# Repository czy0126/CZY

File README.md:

# CZY — 48 V → 约 2 V 薄型固定变比 DCX

**D1 当前设计目标：** 约 24:1 固定比、100 A 输出目标、整机高度 ≤16 mm；成本暂不限制。D2 的 120 A 与 D3 的 ≤10 mm 均后置，保护、绝缘、载流与制造签核不可省。

> **当前研发分支：[`feat/d1-fab-package`](https://github.com/czy0126/CZY/tree/feat/d1-fab-package)。默认 `main` 仍是历史快照。当前 D1 为 `NOT_FOR_FAB`；真实样机尚未获得投板或额定许可。**

## 从这里开始（不用翻旧审核报告）

1. **[D1 当前交接面板](docs/D1_CURRENT.md)**：唯一当前可编辑 G1 原生 PCB、已发生的 ECO、三条并行任务及下一次操作/验收。
2. **[D1 已决事项与重开条件](docs/D1_DECISIONS.md)**：R8/R6、Lr XY、九根布线预检、100 A 铜路等已经确认的边界；禁止重复审查同一证据。
3. **[第49章：D1 G1→G2→G3 交付合同](docs/D1_EXECUTION_KIT/49_D1主功率板PCB唯一执行计划_2026-11-09.md)**：阶段目标、冻结条件与实际制造要求；其 11/9 日期快照不覆盖当前 G1 读回。
4. **[历史技术资料索引](docs/D1_REFERENCE_INDEX.md)**：资料在哪里、哪些只作参考。原 README 的长篇历史更新已[归档](docs/archive/README_D1_branch_before_single_entry_2026-11-10.md)，保留所有技术原文和链接。

**唯一任务入口：** [Issue #4 总交付](https://github.com/czy0126/CZY/issues/4)，以及 [#9 原生 PCB/器件](https://github.com/czy0126/CZY/issues/9)、[#12 磁件与接口](https://github.com/czy0126/CZY/issues/12)、[#36 D0 保护](https://github.com/czy0126/CZY/issues/36)。**同时最多 A/B/C 三个工程工作包**；不为“再次审核/继续优化”新建总计划。

## 实际应该先做什么

**A 线优先：** 9条控制小信号增量已完成原生重开验收，未连接206→199，Physical 0、Netlist仍1；见[同CAD审核回执](hardware/dcx_main/g1/lr_signal_review_report.json)。下一步处理原生Import Changes逐位号差异、实体Cout和100 A两极铜路，不重复重画已有短线。

```powershell
python -m pytest tools/test_g1_copper_coverage.py tools/test_g1_driver_route_plan.py -q
```

上述测试是回归检查，不替代原生DRC；本轮信号候选及失败回执全部保留，尚待随本轮提交提升基线。B（真实 Maxwell/实体 PAD）与 C（D0 真实关断）并行，不得以模拟或脚本绿色替代实际硬件证据。

**工程和开发规则：** [`CLAUDE.md`](CLAUDE.md) · [`docs/agent/EDA.md`](docs/agent/EDA.md) · [PR 模板](.github/PULL_REQUEST_TEMPLATE.md)。任何 PR 应说明真实产物的**改动前后、原始证据和下一次实际交付**。仅更换“最新计划”标题或重复风险总结不算里程碑。

**制造许可唯一来源：** [`hardware/dcx_main/d1_fabrication_gate.json`](hardware/dcx_main/d1_fabrication_gate.json) 及其相同 CAD 修订版的独立审核证据；历史 JSON 不能混用为 G1 的签核。

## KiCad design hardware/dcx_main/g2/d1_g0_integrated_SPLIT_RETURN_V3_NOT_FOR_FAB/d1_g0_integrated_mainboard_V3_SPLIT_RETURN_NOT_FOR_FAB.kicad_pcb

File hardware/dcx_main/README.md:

# DCX 主功率板 —— 原生原理图（A1）

> **最新状态：NOT_FOR_FAB / A1-WIP。** 本目录已移入当前开发分支，保留嘉立创原生 `.eprj2` 和真实焊盘比对。**`netlist_compare.json:readiness=PARTIAL_PASS` 不是完整原理图或投板验收。**
> 17 个 BOM 真实外围（R7–R10、C13、C101–C112）与**五只磁件（T1–T4、CT）**都已画进原生原理图并逐焊盘核对；
> 但外围仍是**值/MPN 占位件**，磁件的引脚号是**逻辑端子名**而不是厂商端子图，物理端子号/极性、
> GUI ERC 与带网 PCB 全部未完成。详见 [磁件符号逻辑合同](magnetics_symbol_contract.json)、[61 件真实选型登记表](component_decision_register.json)、[厂家 24 个端子回填表](vendor_terminal_request.json) 和 [外部阻塞解除与执行协议](../../docs/D1_外部阻塞解除与测试交付_2026-11-02.md)。

这是 `design/v3/pcb/board_netlist.csv`（由 v3 deck 派生的**金网表**）在嘉立创 EDA Pro 里的
原生可编辑原理图，不是一份新的设计。器件、网络、位号全部来自金网表；本目录只解决一件事：
把 SPICE 的 `G/S/D` 引脚名落到真实封装的**具体焊盘**上，并证明落对了。

项目文件：`dcx_main_board.eprj2`（嘉立创 EDA Pro 4.1.60，`.eprj2` 是 SQLite）。
打开方式：复制到嘉立创客户端的工程目录（本项目已改为 `D:\workshop\LCEDA-Pro\projects\`，
见 `%USERPROFILE%\Documents\LCEDA-Pro\config.json` 的 `APP_PROJECT_DIR`），在客户端里打开即可编辑。
**本仓库只有原理图，没有 PCB**——headless 下 PCB 相关 API 不可用，见下。

## 已验证的结论

| 结论 | 证据 |
|------|------|
| **83 个位号**已放置：金网表 66 只 + BOM 真实外围 17 只，**285 个焊盘**全部有归属（280 个接线、5 个按设计留空） | `pin_footprint_review.csv` |
| 按 A1 任务卡的**六个功能块**绘制，每块有标题文字，块内按功能排列 | `gen/slice_00.js` 的 `labels` |
| 金网表的 193 个引脚展开成 **245 个焊盘**，逐焊盘比对**无一错接、无一漏接** | `netlist_compare.json:pads_checked` |
| 17 个外围的 **34 个焊盘**按 `pin_connections.csv` 连接并单独计数，不混进金网表的 245 | `peripheral_pads_checked` |
| U2（UCC27282）裸露焊盘按设计接 PGND，单独计数，**不算进**金网表的 245 | `pads_bonded_by_design` |
| T1–T4、CT **已放置并逐焊盘核对**，引脚号是逻辑端子名（`PRI_A`/`SEC_A`/`CTAP`），**不是**厂商端子号 | `magnetics_symbol_contract.json` |
| 五只磁件的**物理端子号与 DOT 仍未核实**，所有 `physical_pad` 保持 null | `physical_pad_map_verified: false` |
| 83 个位号里 **61 个仍是占位件**（39 原有 + 22 新增外围/磁件；值未定或封装不对），审表里逐行标注 `PLACEHOLDER` | `pin_footprint_review.csv` 的 `note` 列 |

比对是按**焊盘**做的，不是按位号数量做的。这一步是必要的：金网表把 MOS 的引脚叫 `S`，
而 DFN/TDSON 封装的源极是 1、2、3 三个焊盘——只连其中一个，导出的网表仍然"和金网表一致"，
错误要到出铜箔才暴露。

## 评审用的导出图

**`main_board.svg` 目前是过期的**（仍停在磁件放上去之前的 78 个位号）。加进五只磁件后
`getSvgFile` 在 60 s 的 invoke 上限内返回不了：实测两次都在 59750 ms 超时
（`REQUEST_TIMEOUT`），而 CLI 的单次上限写死在 60000 ms。要么在 GUI 里导出，
要么等 A1 收尾时再试。**不要把旧 SVG 当作当前图的证据。**

导出的用法（`gen/export_svg.js` 调 `sch_ManufactureData.getSvgFile`）：

```bash
/d/lceda-pro/lceda-pro.exe invoke --session <id> --ext-uuid eda --timeout 60000 \
    --code "$(cat hardware/dcx_main/gen/export_svg.js)" > /tmp/svg.json
python -c "import json;open('hardware/dcx_main/main_board.svg','w',encoding='utf-8') \
    .write(json.load(open('/tmp/svg.json',encoding='utf-8'))['value']['svg'])"
```

`getSvgFile` 返回整个文件，CLI 输出很大，所以必须重定向；`getPngFile` 也在，但 SVG 可读、可比对。

## 图纸怎么分区

A1 任务卡要求按六部分绘图，`tools/main_board_schematic.py` 的 `SECTIONS` 就是这六块，
放置顺序按信号链：输入/半桥 → 谐振腔与 T1–T4 → 四组 SR → 控制（UCC25600/UCC27282）
→ 偏置/OC/启动 → 输出接口。每块画一个标题文字。

`test_every_placed_ref_sits_in_exactly_one_section` 要求**每个位号恰好落在一块里**：
少一块会被发现（否则器件留在原地），多一块也会被发现（否则被放两次）。
测试还把 `SECTIONS` 的全部位号与金网表的 66 个位号做了集合相等——新增/删除位号不会静默掉队。

审表的 `review_status` 只有四种取值：`MAPPED`、`BONDED BY DESIGN`、`OPEN - REASON GIVEN`、
`OPEN - NEEDS DECISION`。最后一个必须是空的——留一格空白和"已审过"看起来一模一样，
所以测试 `test_every_review_row_carries_a_status_and_a_basis` 直接把它当失败条件。

## 引脚映射从哪来

`library_pins.json` 是对运行中的嘉立创 EDA 客户端**实测**导出的（`gen/probe_all_pins.js`，
按精确 MPN 搜索解析器件，不依赖记忆里的 uuid）。模块里没有任何猜出来的引脚号：

- 器件引脚号覆盖不到金网表的引脚名 → `MappingError` 直接抛错，不静默跳过；
- 一个焊盘被两个不同网络认领 → 同样抛错（这是短路）。

`tools/test_main_board_schematic.py` 会**重新**从 `library_pins.json` 推导 MOS 的 G/S/D 焊盘组，
再和代码里的常量比对——库版本更新导致焊盘重新编号时，红的应该是这个测试。

## 与金网表的唯一一处偏离

`U2` 的焊盘 11 是 VSON-10 的**裸露焊盘**，SPICE 模型里没有它，金网表无从表达。
它在实际器件上是散热路径，也是门驱动开关所参考的电位，悬空是错的，因此接 `PGND`。
这一行在审表里写作 `BONDED BY DESIGN`，在 `netlist_compare.json` 里进
`pads_bonded_by_design` 而不是进 `pads_checked`——**不把它混进金网表的数字里**。

`D_CT1..4` 焊盘 2（BAT54 的第二只阳极）和 `U2` 焊盘 2（datasheet 标 NC）留空，
审表里写明了理由；工具会把"留空"和"漏画"分别报告。

## 金网表之外：17 个真实外围

金网表由 SPICE deck 派生，**表达不了** EN/RUN 默认电平、手动 RUN 跳线、EN 滤波和每只控制 IC 的
VDD 去耦。它们由 `main_board_schematic.py:PERIPHERALS` 单独声明，**不塞进金网表**——
否则"deck 完整"就会被误读成"板子完整"，而制造门槛也就失去了区分能力。

| 位号 | 连接 | BOM 冻结值 |
|---|---|---|
| R7 | RUN–PGND | 10 kΩ |
| R8 | VCC12–RUN（手动 RUN 跳线） | 1 kΩ |
| R9 | GD1–PGND（U2 HI 默认关断） | 10 kΩ |
| R10 | GD2–PGND（U2 LI 默认关断） | 10 kΩ |
| C13 | RUN–PGND（U2 EN 滤波） | 1 nF |
| C101/C102 … C111/C112 | 每只 IC 的 VDD–PGND | 1 µF + 100 nF |

网络名取自 `design/v1/pin_connections.csv` 的**引脚位置**：U2.6=EN 在金网表里叫 `RUN`，
U2.7/8=HI/LI 叫 `GD1`/`GD2`；`12V_P` 在金网表里叫 `VCC12`。测试
`test_every_peripheral_net_is_a_net_the_golden_netlist_already_uses` 锁住这一点，
防止把 CSV 的名字直接搬进原理图、造出一个没人共享的网络（那种错误在图上看起来完全正常）。

它们**不是**新设计：BOM 已有这些行、值已冻结；缺的是 MPN/封装与布局。所以审表仍标
`PLACEHOLDER`，制造门槛也仍不会因为"17 只都画了"而变绿。

## ERC：本站这一轮**不能**用 CLI 签核

`eda.sch_Drc.check()` 是这次客户端里唯一可用的电气规则入口（`Object.getOwnPropertyNames`
显示 `sch_Drc` 原型上只有 `constructor` 和 `check`，没有 `getCheckErrorList` 之类能取明细的接口）。
它 `verbose=false` 返回布尔、`verbose=true` 返回 `[{type, count}]` 直方图，**两个都不给明细**。

实测这个直方图**不随图页内容变化**，所以它的数字不能当 ERC 结论引用：

| 页面状态 | `check(true,false,true)` |
|----------|--------------------------|
| 61 个器件、222 根线 | `warn ×5` |
| 额外放一只**完全未连线的**电阻 | `warn ×5`（不变） |
| 删掉该电阻 | `warn ×5`（不变） |
| **清空整页**（0 个器件） | **`warn ×8`**（反而更多） |

清空后反而变多，说明这个计数不是"这张图页的 ERC 结果"。复现脚本：
`gen/drc_ab.js`、`gen/drc_empty_test.js`（后者会清空图页，跑完必须用
`python tools/lceda_place_main_board.py --all` 恢复）。

**所以 ERC 必须在 GUI 里手工跑一次并截图存档**，本目录不提供 ERC 通过的证据。
这一点写在这里，是为了防止后来者把"5 个 warning"当成一个已知的、已被解释掉的数字。

## 重新生成

```bash
python tools/main_board_schematic.py --write      # -> placement_plan.json + pin_footprint_review.csv
python tools/lceda_place_main_board.py --emit     # -> gen/slice_NN.js
# 必须按路径打开，且在本会话里不要再调 dmt_Project.openProject(uuid)
/d/lceda-pro/lceda-pro.exe open --path "$(pwd -W)/hardware/dcx_main/dcx_main_board.eprj2" --headless true
python tools/lceda_place_main_board.py --all --session <id> --watch hardware/dcx_main/dcx_main_board.eprj2
python tools/lceda_place_main_board.py --netlist-ready --session <id>   # 仅内存，见下
/d/lceda-pro/lceda-pro.exe invoke --session <id> --ext-uuid eda --timeout 60000 \
    --code "$(cat hardware/dcx_main/gen/export_netlist.js)" > hardware/dcx_main/gen/netlist_export_raw.json
python tools/check_main_board_netlist.py          # A4 验收：ok 必须为 True
```

`--session` 是客户端 CLI 会话 id；一次 invoke 上限 **60000 ms**（`--help` 里写的 1800000 是错的）。
放置分 4 片跑，`slice_00.js` 会先清空图页，所以**重跑 `--all` 就是完整的重建**。

三条 headless 实测规律，违反任何一条都会得到"看起来成功、其实没写盘"的结果：

1. **只能用 `--path` 打开工程**。在脚本里调 `dmt_Project.openProject(uuid)` 会让编辑器重新解析到
   云端/库里的副本，此后每次 `sch_Document.save()` 都返回 false、文件 mtime 不变。
   `getCurrentProjectInfo().uuid` 才是工程 uuid，`data[0]` 是名为 `Board1` 的板子而不是工程。
2. **`save()` 是防抖的**：返回 true 之后约 20 s 文件才变大。`--watch` 就是等这个变化；
   只看到 true 不能当作已写盘。
3. **保存与导出互斥**。项目库里的磁件器件带不上封装，而 `getNetlistFile()` 在磁件没有封装时
   什么都不返回；可一旦把 `otherProperty.Footprint` 注入已放置的实例，该文档就**无法再序列化**
   （save 恒 false），而且 `modify()` 会把这个字段搬进实例的 `footprint.uuid`。
   所以顺序固定：**先写盘，再用 `--netlist-ready` 在内存里注入封装 uuid，然后导出**；
   注入之后不能再 save，也不会写进 `.eprj2`。仓库里保存的原生工程因此没有磁件封装关联，
   网表证据来自那一步内存注入。

## 已知缺口（本目录没有假装它们不存在）

1. **磁件的物理端子仍未核实**（原来的"没有符号"已解决）：`DCX_XFMR_5P` / `DCX_CT_4P`
   两个原生符号已建、已放置，引脚号是逻辑端子名。缺的是绕组厂的端子图，把
   `PRI_A`/`SEC_A`/`CTAP` 变成带 DOT 的编号焊盘。在那之前 `physical_pad` 全部是 null，
   `physical_pad_map_verified` 全部是 false——**名字对不等于极性对**。
2. **磁件的封装是占位件**：CT 的符号有 4 个端子，占位封装 `XFMR-TH_ZHT104A` 只有 2 个焊盘；
   变压器用 `XFMR-TH_5P-L20.5-W18.0-P3.25-TL`（5 焊盘）只是为了焊盘数对得上。
   它们让网表能导出、能比对，但不代表能投板。
3. **占位件**：Lr、Cr、Cin、Cout、D_BT 以及全部 R/C 的值仍是 `TO ASSIGN`，
   审表逐行标 `PLACEHOLDER`；它们连的是**对**的网络，但**不是**设计选定的料。
4. **没有 PCB**：`pcb_Document.importChanges` 返回 true 但导入 0 个器件，
   `dmt_Pcb.createPcb` 返回 undefined，`pcb_PrimitiveComponent.create` 抛 `[object Object]`。
   导入 PCB 需要在 GUI 里手工完成。
5. **没有网络表同步回路**：本目录的网表比对证明"原理图 = 金网表"，不证明
   "PCB = 原理图"。后者要靠 GUI 的导入和 DRC。

## 目录

```
dcx_main_board.eprj2          原生工程（可编辑，83 个位号）
library_pins.json             实测的器件引脚（11 类，来源 gen/pins_probe.json）
project_symbols.json          项目库里自建磁件符号的实测 uuid（由 gen/make_project_symbols.js 写入）
magnetics_symbol_contract.json 五只磁件的逻辑端子合同（由 tools/magnetics_cad_contract.py 生成）
placement_plan.json           每个位号 -> 器件 uuid + 焊盘->网络
pin_footprint_review.csv      A3 审表：285 行，含未接线焊盘的理由
netlist_compare.json          A4 比对结果
gen/probe_all_pins.js         按 MPN 实测引脚
gen/make_project_symbols.js   建两个磁件符号并回填 project_symbols.json
gen/export_netlist.js         导出客户端自己的网表
gen/slice_NN.js               放置脚本（由 --emit 生成）
gen/drc_ab.js                 证明 CLI ERC 直方图不随页面变化的实验
gen/drc_empty_test.js         清空页面再测 ERC（破坏性，跑完要 --all 恢复）
gen/api_probe.js              证明 eda.* 不是"什么都返回函数"的桩
gen/export_svg.js             导出评审用 SVG
main_board.svg                上述导出结果（2048×5273）——**已过期**，见上文
```

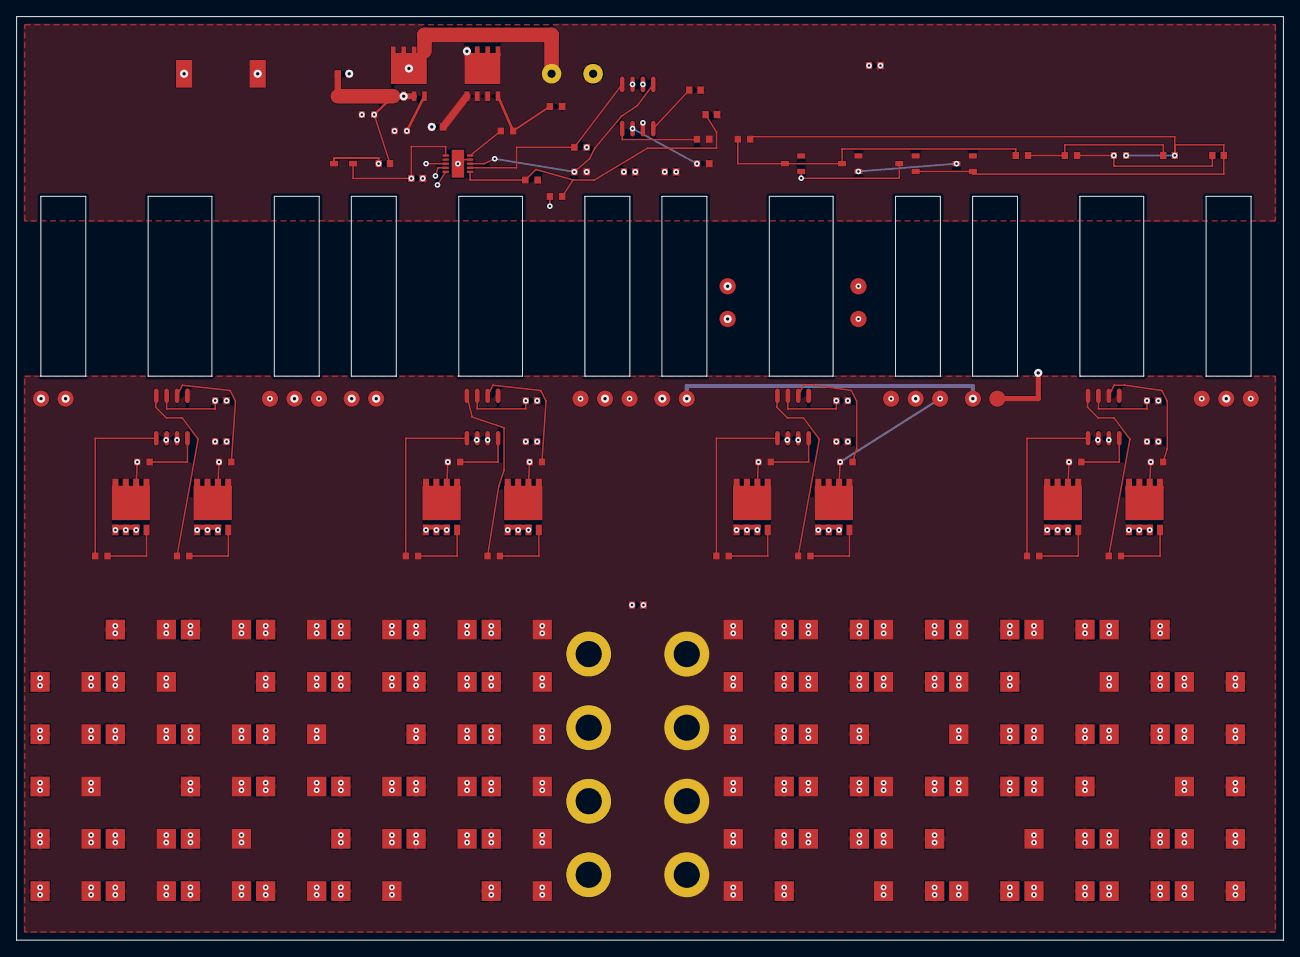
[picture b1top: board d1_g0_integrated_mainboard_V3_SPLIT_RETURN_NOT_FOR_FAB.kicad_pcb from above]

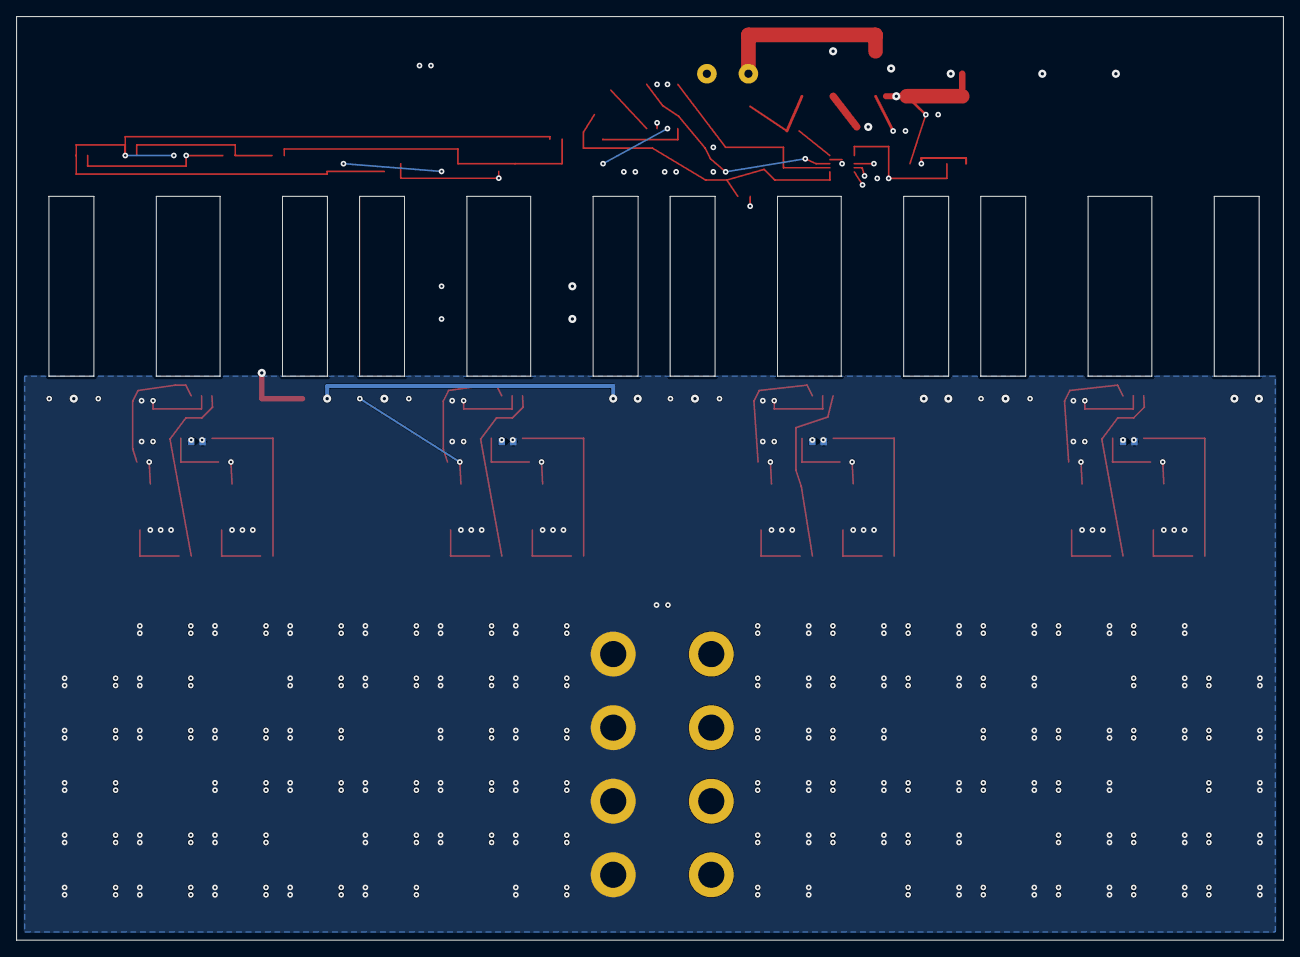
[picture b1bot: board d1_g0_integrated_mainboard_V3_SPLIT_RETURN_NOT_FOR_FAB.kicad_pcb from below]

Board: 12 copper layers, 155.0 x 113.0 mm, 155 parts (4 on the bottom side), 66 nets.

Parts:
C5, C6, C7, C8, C9, C10, C11, C12, C13, C101, C102, C103, C104, C105, C106, C107, C108, C109, C110, C111, C112: V15_PROVISIONAL_CAD_ONLY
CHB01, CHB02, CHB03, CHB04, CHB05, CHB06, CHB07, CHB08, CHB09, CHB10, CHB11, CHB12, CHB13, CHB14, CHB15, CHB16, CHB17, CHB18, CHB19, CHB20, CHB21, CHB22, CHB23, CHB24, CHB25, CHB26, CHB27, CHB28, CHB29, CHB30, CHB31, CHB32, CHB33, CHB34, CHB35, CHB36, CHB37, CHB38, CHB39, CHB40, CHB41, CHB42, CHB43, CHB44, CHB45, CHB46, CHB47, CHB48, CHB49, CHB50, CHB51, CHB52, CHB53, CHB54, CHB55, CHB56, CHB57, CHB58, CHB59, CHB60, CHB61, CHB62, CHB63, CHB64, CHB65, CHB66, CHB67, CHB68, CHB69, CHB70, CHB71, CHB72: T530X477M006ATE004; KEMET_T530X_7343_43_OEM_B
CT: LOGICAL_4LAND_CT_NOT_VENDOR_PINOUT
Cin: V15_PROVISIONAL_CAD_ONLY
Cout: V15_PROVISIONAL_CAD_ONLY
Cr: V15_PROVISIONAL_CAD_ONLY
D_BT: V15_PROVISIONAL_CAD_ONLY
D_CT1, D_CT2, D_CT3, D_CT4: V15_PROVISIONAL_CAD_ONLY
J_IN: V15_PROVISIONAL_CAD_ONLY
J_OUT: EIGHT_PLATED_CONTACTS_VENDOR_UNRATED_NOT_FOR_FAB
Lr: V15_PROVISIONAL_CAD_ONLY
QH: V15_PROVISIONAL_CAD_ONLY
QL: V15_PROVISIONAL_CAD_ONLY
R1, R2, R3, R4, R5, R7, R9, R10, R15, R16, R17, R18, R19, R20, R21, R22, R23, R24, R25, R26, R27, R28, R29, R30, R31, R32, R33, R34, R35: V15_PROVISIONAL_CAD_ONLY
R8: 1k_DNP_UNTIL_EXTERNAL_PERMIT_TESTED
SR1A, SR1B, SR2A, SR2B, SR3A, SR3B, SR4A, SR4B: V15_PROVISIONAL_CAD_ONLY
T1, T2, T3, T4: LOGICAL_5LAND_NOT_VENDOR_PINOUT_NOT_FOR_FAB
U1, U2, U3, U4, U5, U6: V15_PROVISIONAL_CAD_ONLY

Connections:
CR_CT: CT.PRI_A, Cr.2
CS1: CT.SEC_A, D_CT1.1, D_CT3.3
CS2: CT.SEC_B, D_CT2.1, D_CT4.3
CT_LR: CT.PRI_B, Lr.1
DT: R1.1, U1.1
GA1: R20.2, SR1A.4
GA2: R22.2, SR2A.4
GA3: R24.2, SR3A.4
GA4: R26.2, SR4A.4
GB1: R21.2, SR1B.4
GB2: R23.2, SR2B.4
GB3: R25.2, SR3B.4
GB4: R27.2, SR4B.4
GD1: R9.1, U1.8, U2.7
GD2: R10.1, U1.5, U2.8
GH: QH.4, R4.2, R18.1
GH_DRV: R4.1, U2.4
GL: QL.4, R5.2, R19.1
GL_DRV: R5.1, U2.10
HB: C5.1, D_BT.1, U2.3
OC: C12.1, R16.2, R17.1, U1.3
OC1: C11.1, R15.2, R16.1
OCD: D_CT1.3, D_CT2.3, R3.1, R15.1
OCM: C11.2, C12.2, D_CT3.1, D_CT4.1, R3.2, R17.2
PGND: C6.2, C13.2, C101.2, C102.2, C103.2, C104.2, Cin.2, J_IN.2, QL.1, QL.2, QL.3, R1.2, R2.2, R7.2, R9.2, R10.2, R19.2, T4.PRI_B, U1.6, U2.9, U2.11
PRI_12: T1.PRI_B, T2.PRI_A
PRI_23: T2.PRI_B, T3.PRI_A
PRI_34: T3.PRI_B, T4.PRI_A
PRI_T1: Lr.2, T1.PRI_A
REG1: C7.1, U3.3
REG2: C8.1, U4.3
REG3: C9.1, U5.3
REG4: C10.1, U6.3
RT: R2.1, U1.2
RUN: C13.1, R7.1, R8.2, U2.6
SEC1_A: R28.1, SR1A.5, SR1A.6, SR1A.7, SR1A.8, T1.SEC_A
SEC1_B: R29.1, SR1B.5, SR1B.6, SR1B.7, SR1B.8, T1.SEC_B
SEC2_A: R30.1, SR2A.5, SR2A.6, SR2A.7, SR2A.8, T2.SEC_A
SEC2_B: R31.1, SR2B.5, SR2B.6, SR2B.7, SR2B.8, T2.SEC_B
SEC3_A: R32.1, SR3A.5, SR3A.6, SR3A.7, SR3A.8, T3.SEC_A
SEC3_B: R33.1, SR3B.5, SR3B.6, SR3B.7, SR3B.8, T3.SEC_B
SEC4_A: R34.1, SR4A.5, SR4A.6, SR4A.7, SR4A.8, T4.SEC_A
SEC4_B: R35.1, SR4B.5, SR4B.6, SR4B.7, SR4B.8, T4.SEC_B
SR_SOURCE_RETURN: C7.2, C8.2, C9.2, C10.2, C105.2, C106.2, C107.2, C108.2, C109.2, C110.2, C111.2, C112.2, CHB01.2, CHB02.2, CHB03.2, CHB04.2, CHB05.2, CHB06.2, CHB07.2, CHB08.2, CHB09.2, CHB10.2, CHB11.2, CHB12.2, CHB13.2, CHB14.2, CHB15.2, CHB16.2, CHB17.2, CHB18.2, CHB19.2, CHB20.2, CHB21.2, CHB22.2, CHB23.2, CHB24.2, CHB25.2, CHB26.2, CHB27.2, CHB28.2, CHB29.2, CHB30.2, CHB31.2, CHB32.2, CHB33.2, CHB34.2, CHB35.2, CHB36.2, CHB37.2, CHB38.2, CHB39.2, CHB40.2, CHB41.2, CHB42.2, CHB43.2, CHB44.2, CHB45.2, CHB46.2, CHB47.2, CHB48.2, CHB49.2, CHB50.2, CHB51.2, CHB52.2, CHB53.2, CHB54.2, CHB55.2, CHB56.2, CHB57.2, CHB58.2, CHB59.2, CHB60.2, CHB61.2, CHB62.2, CHB63.2, CHB64.2, CHB65.2, CHB66.2, CHB67.2, CHB68.2, CHB69.2, CHB70.2, CHB71.2, CHB72.2, Cout.2, J_OUT.2, SR1A.1, SR1A.2, SR1A.3, SR1B.1, SR1B.2, SR1B.3, SR2A.1, SR2A.2, SR2A.3, SR2B.1, SR2B.2, SR2B.3, SR3A.1, SR3A.2, SR3A.3, SR3B.1, SR3B.2, SR3B.3, SR4A.1, SR4A.2, SR4A.3, SR4B.1, SR4B.2, SR4B.3, U3.2, U3.5, U4.2, U4.5, U5.2, U5.5, U6.2, U6.5
SS: C6.1, U1.4
SW: C5.2, Cr.1, QH.1, QH.2, QH.3, QL.5, QL.6, QL.7, QL.8, QL.9, R18.2, U2.5
VCC12: C101.1, C102.1, C103.1, C104.1, D_BT.2, R8.1, U1.7, U2.1
VCC12_S: C105.1, C106.1, C107.1, C108.1, C109.1, C110.1, C111.1, C112.1, U3.7, U4.7, U5.7, U6.7
VD1_A: R28.2, U3.4
VD1_B: R29.2, U3.6
VD2_A: R30.2, U4.4
VD2_B: R31.2, U4.6
VD3_A: R32.2, U5.4
VD3_B: R33.2, U5.6
VD4_A: R34.2, U6.4
VD4_B: R35.2, U6.6
VG1_A: R20.1, U3.1
VG1_B: R21.1, U3.8
VG2_A: R22.1, U4.1
VG2_B: R23.1, U4.8
VG3_A: R24.1, U5.1
VG3_B: R25.1, U5.8
VG4_A: R26.1, U6.1
VG4_B: R27.1, U6.8
VIN_P: Cin.1, J_IN.1, QH.5, QH.6, QH.7, QH.8, QH.9
VOUT: CHB01.1, CHB02.1, CHB03.1, CHB04.1, CHB05.1, CHB06.1, CHB07.1, CHB08.1, CHB09.1, CHB10.1, CHB11.1, CHB12.1, CHB13.1, CHB14.1, CHB15.1, CHB16.1, CHB17.1, CHB18.1, CHB19.1, CHB20.1, CHB21.1, CHB22.1, CHB23.1, CHB24.1, CHB25.1, CHB26.1, CHB27.1, CHB28.1, CHB29.1, CHB30.1, CHB31.1, CHB32.1, CHB33.1, CHB34.1, CHB35.1, CHB36.1, CHB37.1, CHB38.1, CHB39.1, CHB40.1, CHB41.1, CHB42.1, CHB43.1, CHB44.1, CHB45.1, CHB46.1, CHB47.1, CHB48.1, CHB49.1, CHB50.1, CHB51.1, CHB52.1, CHB53.1, CHB54.1, CHB55.1, CHB56.1, CHB57.1, CHB58.1, CHB59.1, CHB60.1, CHB61.1, CHB62.1, CHB63.1, CHB64.1, CHB65.1, CHB66.1, CHB67.1, CHB68.1, CHB69.1, CHB70.1, CHB71.1, CHB72.1, Cout.1, J_OUT.1, T1.CTAP, T2.CTAP, T3.CTAP, T4.CTAP

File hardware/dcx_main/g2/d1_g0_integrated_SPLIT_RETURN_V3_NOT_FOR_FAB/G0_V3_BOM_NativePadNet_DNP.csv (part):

Ref,DesignMPN_UNQUALIFIED,NativeValue,DNP,PhysicalPadObjects,RefPadNet,QualifiedForFab
C10,C0603_100n,V15_PROVISIONAL_CAD_ONLY,no,2,1=REG4;2=SR_SOURCE_RETURN,no
C101,C0603_100n (design value from peripheral register; OEM not qualified),V15_PROVISIONAL_CAD_ONLY,no,2,1=VCC12;2=PGND,no
C102,C0603_100n (design value from peripheral register; OEM not qualified),V15_PROVISIONAL_CAD_ONLY,no,2,1=VCC12;2=PGND,no
C103,C0603_100n (design value from peripheral register; OEM not qualified),V15_PROVISIONAL_CAD_ONLY,no,2,1=VCC12;2=PGND,no
C104,C0603_100n (design value from peripheral register; OEM not qualified),V15_PROVISIONAL_CAD_ONLY,no,2,1=VCC12;2=PGND,no
C105,C0603_100n (design value from peripheral register; OEM not qualified),V15_PROVISIONAL_CAD_ONLY,no,2,1=VCC12_S;2=SR_SOURCE_RETURN,no
C106,C0603_100n (design value from peripheral register; OEM not qualified),V15_PROVISIONAL_CAD_ONLY,no,2,1=VCC12_S;2=SR_SOURCE_RETURN,no
C107,C0603_100n (design value from peripheral register; OEM not qualified),V15_PROVISIONAL_CAD_ONLY,no,2,1=VCC12_S;2=SR_SOURCE_RETURN,no
C108,C0603_100n (design value from peripheral register; OEM not qualified),V15_PROVISIONAL_CAD_ONLY,no,2,1=VCC12_S;2=SR_SOURCE_RETURN,no
C109,C0603_100n (design value from peripheral register; OEM not qualified),V15_PROVISIONAL_CAD_ONLY,no,2,1=VCC12_S;2=SR_SOURCE_RETURN,no
C11,C0603_100n,V15_PROVISIONAL_CAD_ONLY,no,2,1=OC1;2=OCM,no
C110,C0603_100n (design value from peripheral register; OEM not qualified),V15_PROVISIONAL_CAD_ONLY,no,2,1=VCC12_S;2=SR_SOURCE_RETURN,no
C111,C0603_100n (design value from peripheral register; OEM not qualified),V15_PROVISIONAL_CAD_ONLY,no,2,1=VCC12_S;2=SR_SOURCE_RETURN,no
C112,C0603_100n (design value from peripheral register; OEM not qualified),V15_PROVISIONAL_CAD_ONLY,no,2,1=VCC12_S;2=SR_SOURCE_RETURN,no
C12,C0603_100n,V15_PROVISIONAL_CAD_ONLY,no,2,1=OC;2=OCM,no
C13,C0603_100n (design value from peripheral register; OEM not qualified),V15_PROVISIONAL_CAD_ONLY,no,2,1=RUN;2=PGND,no
C5,C0603_100n,V15_PROVISIONAL_CAD_ONLY,no,2,1=HB;2=SW,no
C6,C0603_100n,V15_PROVISIONAL_CAD_ONLY,no,2,1=SS;2=PGND,no
C7,C0603_100n,V15_PROVISIONAL_CAD_ONLY,no,2,1=REG1;2=SR_SOURCE_RETURN,no
C8,C0603_100n,V15_PROVISIONAL_CAD_ONLY,no,2,1=REG2;2=SR_SOURCE_RETURN,no
C9,C0603_100n,V15_PROVISIONAL_CAD_ONLY,no,2,1=REG3;2=SR_SOURCE_RETURN,no
CHB01,"T530 OEM tentative, MPN and derating require signoff",T530X477M006ATE004,no,2,1=VOUT;2=SR_SOURCE_RETURN,no
CHB02,"T530 OEM tentative, MPN and derating require signoff",T530X477M006ATE004,no,2,1=VOUT;2=SR_SOURCE_RETURN,no
CHB03,"T530 OEM tentative, MPN and derating require signoff",T530X477M006ATE004,no,2,1=VOUT;2=SR_SOURCE_RETURN,no
CHB04,"T530 OEM tentative, MPN and derating require signoff",T530X477M006ATE004,no,2,1=VOUT;2=SR_SOURCE_RETURN,no
CHB05,"T530 OEM tentative, MPN and derating require signoff",T530X477M006ATE004,no,2,1=VOUT;2=SR_SOURCE_RETURN,no
CHB06,"T530 OEM tentative, MPN and derating require signoff",T530X477M006ATE004,no,2,1=VOUT;2=SR_SOURCE_RETURN,no
CHB07,"T530 OEM tentative, MPN and derating require signoff",T530X477M006ATE004,no,2,1=VOUT;2=SR_SOURCE_RETURN,no
CHB08,"T530 OEM tentative, MPN and derating require signoff",T530X477M006ATE004,no,2,1=VOUT;2=SR_SOURCE_RETURN,no
CHB09,"T530 OEM tentative, MPN and derating require signoff",T530X477M006ATE004,no,2,1=VOUT;2=SR_SOURCE_RETURN,no
CHB10,"T530 OEM tentative, MPN and derating require signoff",T530X477M006ATE004,no,2,1=VOUT;2=SR_SOURCE_RETURN,no
CHB11,"T530 OEM tentative, MPN and derating require signoff",T530X477M006ATE004,no,2,1=VOUT;2=SR_SOURCE_RETURN,no
CHB12,"T530 OEM tentative, MPN and derating require signoff",T530X477M006ATE004,no,2,1=VOUT;2=SR_SOURCE_RETURN,no
CHB13,"T530 OEM tentative, MPN and derating require signoff",T530X477M006ATE004,no,2,1=VOUT;2=SR_SOURCE_RETURN,no
CHB14,"T530 OEM tentative, MPN and derating require signoff",T530X477M006ATE004,no,2,1=VOUT;2=SR_SOURCE_RETURN,no
CHB15,"T530 OEM tentative, MPN and derating require signoff",T530X477M006ATE004,no,2,1=VOUT;2=SR_SOURCE_RETURN,no
CHB16,"T530 OEM tentative, MPN and derating require signoff",T530X477M006ATE004,no,2,1=VOUT;2=SR_SOURCE_RETURN,no
CHB17,"T530 OEM tentative, MPN and derating require signoff",T530X477M006ATE004,no,2,1=VOUT;2=SR_SOURCE_RETURN,no
CHB18,"T530 OEM tentative, MPN and derating require signoff",T530X477M006ATE004,no,2,1=VOUT;2=SR_SOURCE_RETURN,no
CHB19,"T530 OEM tentative, MPN and derating require signoff",T530X477M006ATE004,no,2,1=VOUT;2=SR_SOURCE_RETURN,no
CHB20,"T530 OEM tentative, MPN and derating require signoff",T530X477M006ATE004,no,2,1=VOUT;2=SR_SOURCE_RETURN,no
CHB21,"T530 OEM tentative, MPN and derating require signoff",T530X477M006ATE004,no,2,1=VOUT;2=SR_SOURCE_RETURN,no
CHB22,"T530 OEM tentative, MPN and derating require signoff",T530X477M006ATE004,no,2,1=VOUT;2=SR_SOURCE_RETURN,no
CHB23,"T530 OEM tentative, MPN and derating require signoff",T530X477M006ATE004,no,2,1=VOUT;2=SR_SOURCE_RETURN,no
CHB24,"T530 OEM tentative, MPN and derating require signoff",T530X477M006ATE004,no,2,1=VOUT;2=SR_SOURCE_RETURN,no
CHB25,"T530 OEM tentative, MPN and derating require signoff",T530X477M006ATE004,no,2,1=VOUT;2=SR_SOURCE_RETURN,no
CHB26,"T530 OEM tentative, MPN and derating require signoff",T530X477M006ATE004,no,2,1=VOUT;2=SR_SOURCE_RETURN,no
CHB27,"T530 OEM tentative, MPN and derating require signoff",T530X477M006ATE004,no,2,1=VOUT;2=SR_SOURCE_RETURN,no
CHB28,"T530 OEM tentative, MPN and derating require signoff",T530X477M006ATE004,no,2,1=VOUT;2=SR_SOURCE_RETURN,no
CHB29,"T530 OEM tentative, MPN and derating require signoff",T530X477M006ATE004,no,2,1=VOUT;2=SR_SOURCE_RETURN,no
CHB30,"T530 OEM tentative, MPN and derating require signoff",T530X477M006ATE004,no,2,1=VOUT;2=SR_SOURCE_RETURN,no
CHB31,"T530 OEM tentative, MPN and derating require signoff",T530X477M006ATE004,no,2,1=VOUT;2=SR_SOURCE_RETURN,no
CHB32,"T530 OEM tentative, MPN and derating require signoff",T530X477M006ATE004,no,2,1=VOUT;2=SR_SOURCE_RETURN,no
CHB33,"T530 OEM tentative, MPN and derating require signoff",T530X477M006ATE004,no,2,1=VOUT;2=SR_SOURCE_RETURN,no
CHB34,"T530 OEM tentative, MPN and derating require signoff",T530X477M006ATE004,no,2,1=VOUT;2=SR_SOURCE_RETURN,no
CHB35,"T530 OEM tentative, MPN and derating require signoff",T530X477M006ATE004,no,2,1=VOUT;2=SR_SOURCE_RETURN,no
CHB36,"T530 OEM tentative, MPN and derating require signoff",T530X477M006ATE004,no,2,1=VOUT;2=SR_SOURCE_RETURN,no
CHB37,"T530 OEM tentative, MPN and derating require signoff",T530X477M006ATE004,no,2,1=VOUT;2=SR_SOURCE_RETURN,no
CHB38,"T530 OEM tentative, MPN and derating require signoff",T530X477M006ATE004,no,2,1=VOUT;2=SR_SOURCE_RETURN,no
CHB39,"T530 OEM tentative, MPN and derating require signoff",T530X477M006ATE004,no,2,1=VOUT;2=SR_SOURCE_RETURN,no
CHB40,"T530 OEM tentative, MPN and derating require signoff",T530X477M006ATE004,no,2,1=VOUT;2=SR_SOURCE_RETURN,no
CHB41,"T530 OEM tentative, MPN and derating require signoff",T530X477M006ATE004,no,2,1=VOUT;2=SR_SOURCE_RETURN,no
CHB42,"T530 OEM tentative, MPN and derating require signoff",T530X477M006ATE004,no,2,1=VOUT;2=SR_SOURCE_RETURN,no
CHB43,"T530 OEM tentative, MPN and derating require signoff",T530X477M006ATE004,no,2,1=VOUT;2=SR_SOURCE_RETURN,no
CHB44,"T530 OEM tentative, MPN and derating require signoff",T530X477M006ATE004,no,2,1=VOUT;2=SR_SOURCE_RETURN,no
CHB45,"T530 OEM tentative, MPN and derating require signoff",T530X477M006ATE004,no,2,1=VOUT;2=SR_SOURCE_RETURN,no
CHB46,"T530 OEM tentative, MPN and derating require signoff",T530X477M006ATE004,no,2,1=VOUT;2=SR_SOURCE_RETURN,no
CHB47,"T530 OEM tentative, MPN and derating require signoff",T530X477M006ATE004,no,2,1=VOUT;2=SR_SOURCE_RETURN,no
CHB48,"T530 OEM tentative, MPN and derating require signoff",T530X477M006ATE004,no,2,1=VOUT;2=SR_SOURCE_RETURN,no
CHB49,"T530 OEM tentative, MPN and derating require signoff",T530X477M006ATE004,no,2,1=VOUT;2=SR_SOURCE_RETURN,no
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
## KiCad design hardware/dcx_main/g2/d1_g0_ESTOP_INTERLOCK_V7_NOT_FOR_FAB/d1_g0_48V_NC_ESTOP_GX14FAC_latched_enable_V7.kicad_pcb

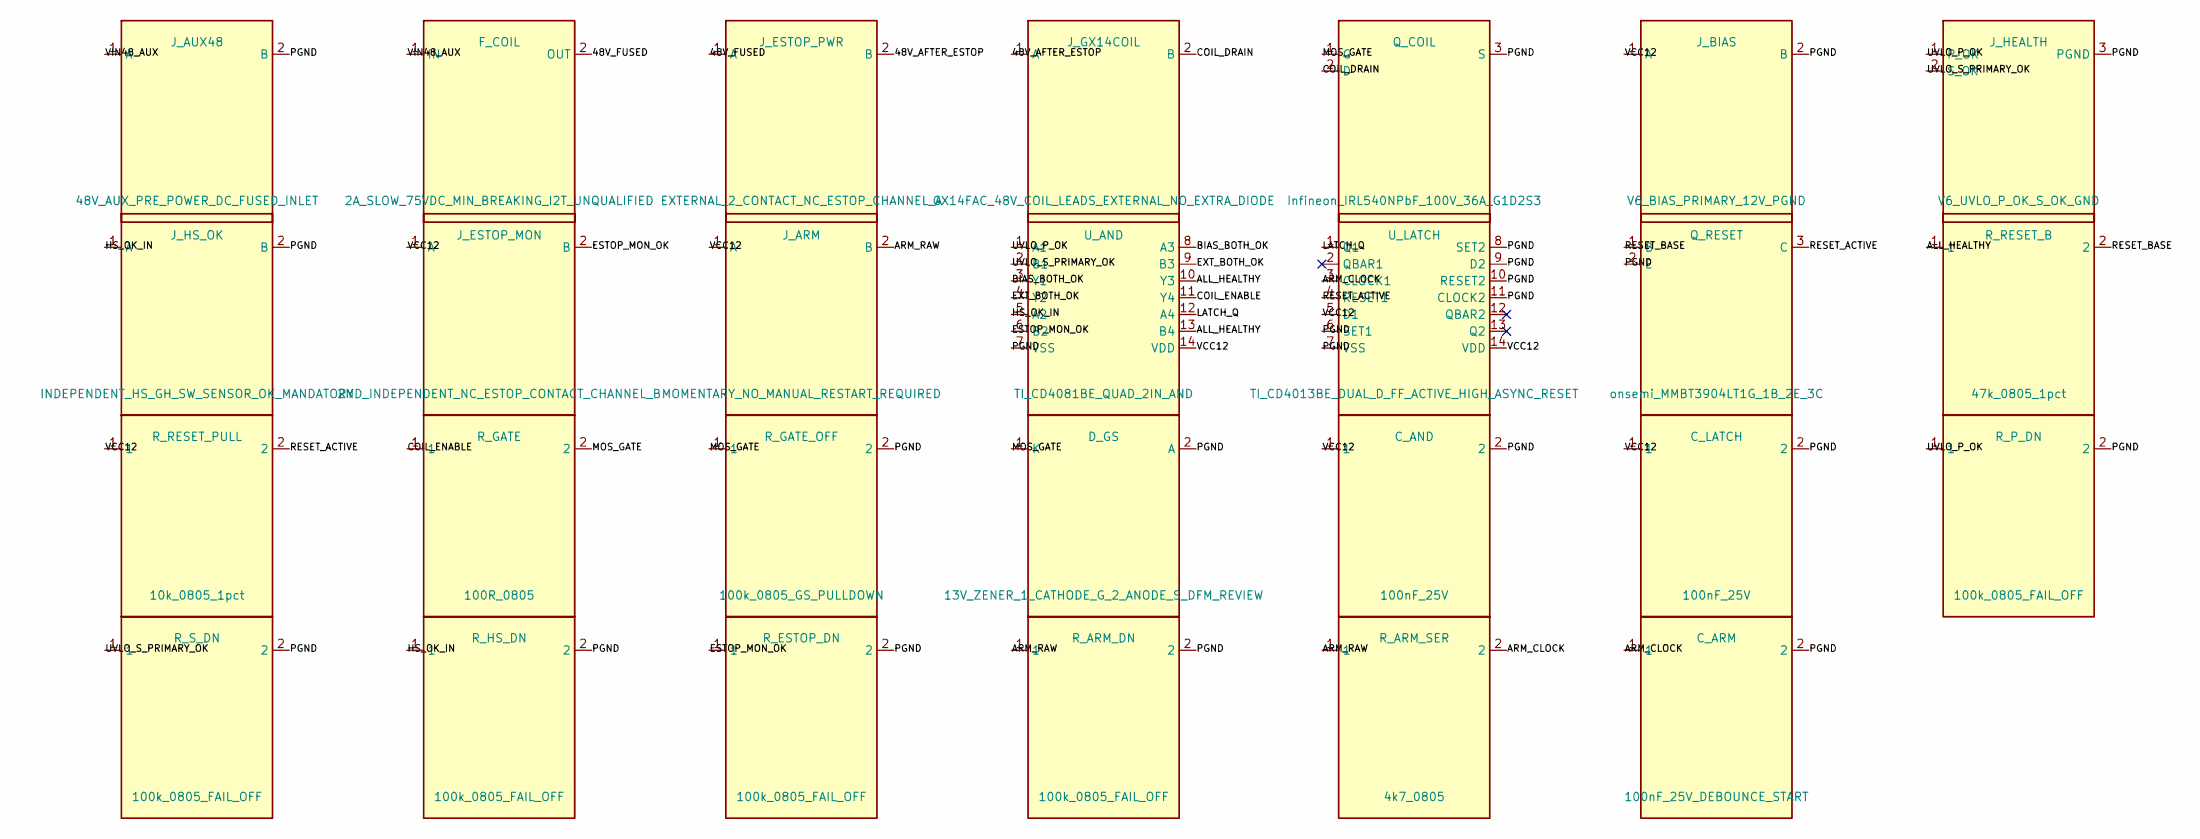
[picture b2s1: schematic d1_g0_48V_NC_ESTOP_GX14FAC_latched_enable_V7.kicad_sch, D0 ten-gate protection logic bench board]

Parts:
C_AND: 100nF_25V; C_0603_1608Metric
C_ARM: 100nF_25V_DEBOUNCE_START; C_0603_1608Metric
C_LATCH: 100nF_25V; C_0603_1608Metric
D_GS: 13V_ZENER_1_CATHODE_G_2_ANODE_S_DFM_REVIEW; D_SOD-123
F_COIL: 2A_SLOW_75VDC_MIN_BREAKING_I2T_UNQUALIFIED; Fuse_1812_4532Metric
J_ARM: MOMENTARY_NO_MANUAL_RESTART_REQUIRED; TerminalBlock_MaiXu_MX126-5.0-02P_1x02_P5.00mm
J_AUX48: 48V_AUX_PRE_POWER_DC_FUSED_INLET; TerminalBlock_MaiXu_MX126-5.0-02P_1x02_P5.00mm
J_BIAS: V6_BIAS_PRIMARY_12V_PGND; TerminalBlock_MaiXu_MX126-5.0-02P_1x02_P5.00mm
J_ESTOP_MON: 2ND_INDEPENDENT_NC_ESTOP_CONTACT_CHANNEL_B; TerminalBlock_MaiXu_MX126-5.0-02P_1x02_P5.00mm
J_ESTOP_PWR: EXTERNAL_2_CONTACT_NC_ESTOP_CHANNEL_A; TerminalBlock_MaiXu_MX126-5.0-02P_1x02_P5.00mm
J_GX14COIL: GX14FAC_48V_COIL_LEADS_EXTERNAL_NO_EXTRA_DIODE; TerminalBlock_MaiXu_MX126-5.0-02P_1x02_P5.00mm
J_HEALTH: V6_UVLO_P_OK_S_OK_GND; PinHeader_1x03_P2.54mm_Vertical
J_HS_OK: INDEPENDENT_HS_GH_SW_SENSOR_OK_MANDATORY; TerminalBlock_MaiXu_MX126-5.0-02P_1x02_P5.00mm
Q_COIL: Infineon_IRL540NPbF_100V_36A_G1D2S3; TO-220-3_Vertical
Q_RESET: onsemi_MMBT3904LT1G_1B_2E_3C; SOT-23
R_ARM_DN: 100k_0805_FAIL_OFF; R_0805_2012Metric
R_ARM_SER: 4k7_0805; R_0805_2012Metric
R_ESTOP_DN: 100k_0805_FAIL_OFF; R_0805_2012Metric
R_GATE: 100R_0805; R_0805_2012Metric
R_GATE_OFF: 100k_0805_GS_PULLDOWN; R_0805_2012Metric
R_HS_DN: 100k_0805_FAIL_OFF; R_0805_2012Metric
R_P_DN: 100k_0805_FAIL_OFF; R_0805_2012Metric
R_RESET_B: 47k_0805_1pct; R_0805_2012Metric
R_RESET_PULL: 10k_0805_1pct; R_0805_2012Metric
R_S_DN: 100k_0805_FAIL_OFF; R_0805_2012Metric
U_AND: TI_CD4081BE_QUAD_2IN_AND; DIP-14_W7.62mm
U_LATCH: TI_CD4013BE_DUAL_D_FF_ACTIVE_HIGH_ASYNC_RESET; DIP-14_W7.62mm

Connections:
48V_AFTER_ESTOP: J_ESTOP_PWR.2 (B), J_GX14COIL.1 (A)
48V_FUSED: F_COIL.2 (OUT), J_ESTOP_PWR.1 (A)
ALL_HEALTHY: R_RESET_B.1, U_AND.10 (Y3), U_AND.13 (B4)
ARM_CLOCK: C_ARM.1, R_ARM_SER.2, U_LATCH.3 (CLOCK1)
ARM_RAW: J_ARM.2 (B), R_ARM_DN.1, R_ARM_SER.1
BIAS_BOTH_OK: U_AND.3 (Y1), U_AND.8 (A3)
COIL_DRAIN: J_GX14COIL.2 (B), Q_COIL.2 (D)
COIL_ENABLE: R_GATE.1, U_AND.11 (Y4)
ESTOP_MON_OK: J_ESTOP_MON.2 (B), R_ESTOP_DN.1, U_AND.6 (B2)
EXT_BOTH_OK: U_AND.4 (Y2), U_AND.9 (B3)
HS_OK_IN: J_HS_OK.1 (A), R_HS_DN.1, U_AND.5 (A2)
LATCH_Q: U_AND.12 (A4), U_LATCH.1 (Q1)
MOS_GATE: D_GS.1 (K), Q_COIL.1 (G), R_GATE.2, R_GATE_OFF.1
PGND: C_AND.2, C_ARM.2, C_LATCH.2, D_GS.2 (A), J_AUX48.2 (B), J_BIAS.2 (B), J_HEALTH.3 (PGND), J_HS_OK.2 (B), Q_COIL.3 (S), Q_RESET.2 (E), R_ARM_DN.2, R_ESTOP_DN.2, R_GATE_OFF.2, R_HS_DN.2, R_P_DN.2, R_S_DN.2, U_AND.7 (VSS), U_LATCH.6 (SET1), U_LATCH.7 (VSS), U_LATCH.8 (SET2), U_LATCH.9 (D2), U_LATCH.10 (RESET2), U_LATCH.11 (CLOCK2)
RESET_ACTIVE: Q_RESET.3 (C), R_RESET_PULL.2, U_LATCH.4 (RESET1)
RESET_BASE: Q_RESET.1 (B), R_RESET_B.2
UVLO_P_OK: J_HEALTH.1 (P_OK), R_P_DN.1, U_AND.1 (A1)
UVLO_S_PRIMARY_OK: J_HEALTH.2 (S_OK), R_S_DN.1, U_AND.2 (B1)
VCC12: C_AND.1, C_LATCH.1, J_ARM.1 (A), J_BIAS.1 (A), J_ESTOP_MON.1 (A), R_RESET_PULL.1, U_AND.14 (VDD), U_LATCH.5 (D1), U_LATCH.14 (VDD)
VIN48_AUX: F_COIL.1 (IN), J_AUX48.1 (A)

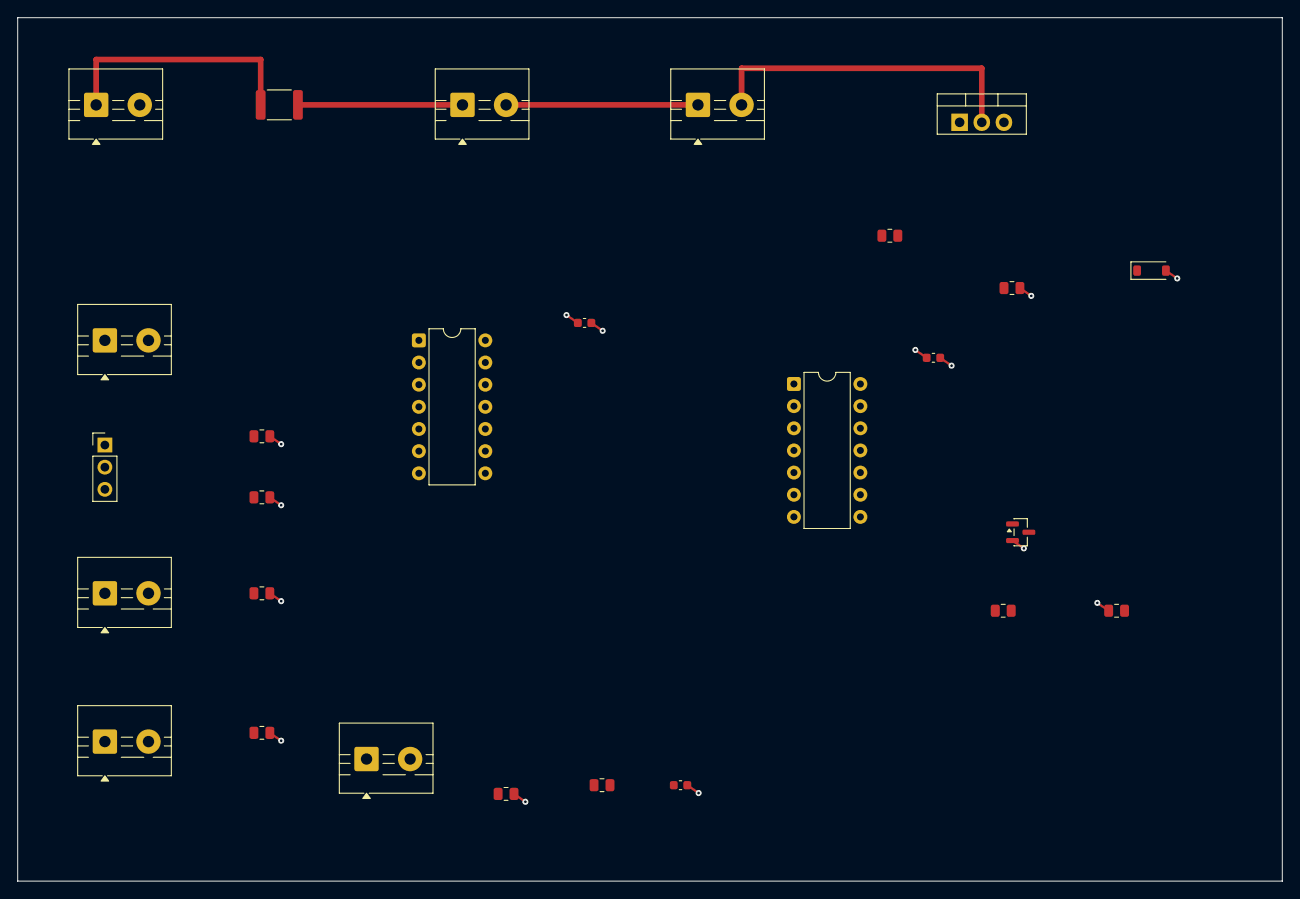
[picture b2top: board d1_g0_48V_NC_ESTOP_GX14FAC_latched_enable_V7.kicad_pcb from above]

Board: 4 copper layers, 145.0 x 99.0 mm, 27 parts (0 on the bottom side), 20 nets.

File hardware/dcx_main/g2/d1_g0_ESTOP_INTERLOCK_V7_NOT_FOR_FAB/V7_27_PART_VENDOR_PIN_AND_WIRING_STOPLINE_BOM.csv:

Ref,Intended_MPN_or_TBD,Native_footprint,Pad_Net,Assembly,Vendor_spec_verified,G0_fab_approved
R_P_DN,100k_0805_FAIL_OFF,Resistor_SMD:R_0805_2012Metric,1=UVLO_P_OK;2=PGND,CANDIDATE_NOT_BUILT,NO,NO
J_HEALTH,V6_UVLO_P_OK_S_OK_GND,Connector_PinHeader_2.54mm:PinHeader_1x03_P2.54mm_Vertical,1=UVLO_P_OK;2=UVLO_S_PRIMARY_OK;3=PGND,EXTERNAL_AND_UNBUILT,NO,NO
R_RESET_B,47k_0805_1pct,Resistor_SMD:R_0805_2012Metric,1=ALL_HEALTHY;2=RESET_BASE,CANDIDATE_NOT_BUILT,NO,NO
R_GATE_OFF,100k_0805_GS_PULLDOWN,Resistor_SMD:R_0805_2012Metric,1=MOS_GATE;2=PGND,CANDIDATE_NOT_BUILT,NO,NO
C_AND,100nF_25V,Capacitor_SMD:C_0603_1608Metric,1=VCC12;2=PGND,CANDIDATE_NOT_BUILT,NO,NO
R_GATE,100R_0805,Resistor_SMD:R_0805_2012Metric,1=COIL_ENABLE;2=MOS_GATE,CANDIDATE_NOT_BUILT,NO,NO
R_ESTOP_DN,100k_0805_FAIL_OFF,Resistor_SMD:R_0805_2012Metric,1=ESTOP_MON_OK;2=PGND,CANDIDATE_NOT_BUILT,NO,NO
Q_COIL,Infineon_IRL540NPbF_100V_36A_G1D2S3,Package_TO_SOT_THT:TO-220-3_Vertical,1=MOS_GATE;2=COIL_DRAIN;3=PGND,CANDIDATE_NOT_BUILT,YES_PIN_OR_SYMBOL_ONLY,NO
R_HS_DN,100k_0805_FAIL_OFF,Resistor_SMD:R_0805_2012Metric,1=HS_OK_IN;2=PGND,CANDIDATE_NOT_BUILT,NO,NO
C_LATCH,100nF_25V,Capacitor_SMD:C_0603_1608Metric,1=VCC12;2=PGND,CANDIDATE_NOT_BUILT,NO,NO
J_AUX48,48V_AUX_PRE_POWER_DC_FUSED_INLET,TerminalBlock:TerminalBlock_MaiXu_MX126-5.0-02P_1x02_P5.00mm,1=VIN48_AUX;2=PGND,EXTERNAL_AND_UNBUILT,NO,NO
J_ARM,MOMENTARY_NO_MANUAL_RESTART_REQUIRED,TerminalBlock:TerminalBlock_MaiXu_MX126-5.0-02P_1x02_P5.00mm,1=VCC12;2=ARM_RAW,EXTERNAL_AND_UNBUILT,NO,NO
J_BIAS,V6_BIAS_PRIMARY_12V_PGND,TerminalBlock:TerminalBlock_MaiXu_MX126-5.0-02P_1x02_P5.00mm,1=VCC12;2=PGND,EXTERNAL_AND_UNBUILT,NO,NO
R_RESET_PULL,10k_0805_1pct,Resistor_SMD:R_0805_2012Metric,1=VCC12;2=RESET_ACTIVE,CANDIDATE_NOT_BUILT,NO,NO
J_ESTOP_MON,2ND_INDEPENDENT_NC_ESTOP_CONTACT_CHANNEL_B,TerminalBlock:TerminalBlock_MaiXu_MX126-5.0-02P_1x02_P5.00mm,1=VCC12;2=ESTOP_MON_OK,EXTERNAL_AND_UNBUILT,NO,NO
Q_RESET,onsemi_MMBT3904LT1G_1B_2E_3C,Package_TO_SOT_SMD:SOT-23,1=RESET_BASE;2=PGND;3=RESET_ACTIVE,CANDIDATE_NOT_BUILT,NO,NO
U_AND,TI_CD4081BE_QUAD_2IN_AND,Package_DIP:DIP-14_W7.62mm,1=UVLO_P_OK;10=ALL_HEALTHY;11=COIL_ENABLE;12=LATCH_Q;13=ALL_HEALTHY;14=VCC12;2=UVLO_S_PRIMARY_OK;3=BIAS_BOTH_OK;4=EXT_BOTH_OK;5=HS_OK_IN;6=ESTOP_MON_OK;7=PGND;8=BIAS_BOTH_OK;9=EXT_BOTH_OK,CANDIDATE_NOT_BUILT,YES_PIN_OR_SYMBOL_ONLY,NO
J_GX14COIL,GX14FAC_48V_COIL_LEADS_EXTERNAL_NO_EXTRA_DIODE,TerminalBlock:TerminalBlock_MaiXu_MX126-5.0-02P_1x02_P5.00mm,1=48V_AFTER_ESTOP;2=COIL_DRAIN,EXTERNAL_AND_UNBUILT,NO,NO
F_COIL,2A_SLOW_75VDC_MIN_BREAKING_I2T_UNQUALIFIED,Fuse:Fuse_1812_4532Metric,1=VIN48_AUX;2=48V_FUSED,CANDIDATE_NOT_BUILT,NO,NO
J_HS_OK,INDEPENDENT_HS_GH_SW_SENSOR_OK_MANDATORY,TerminalBlock:TerminalBlock_MaiXu_MX126-5.0-02P_1x02_P5.00mm,1=HS_OK_IN;2=PGND,EXTERNAL_AND_UNBUILT,NO,NO
R_ARM_DN,100k_0805_FAIL_OFF,Resistor_SMD:R_0805_2012Metric,1=ARM_RAW;2=PGND,CANDIDATE_NOT_BUILT,NO,NO
R_ARM_SER,4k7_0805,Resistor_SMD:R_0805_2012Metric,1=ARM_RAW;2=ARM_CLOCK,CANDIDATE_NOT_BUILT,NO,NO
D_GS,13V_ZENER_1_CATHODE_G_2_ANODE_S_DFM_REVIEW,Diode_SMD:D_SOD-123,1=MOS_GATE;2=PGND,CANDIDATE_NOT_BUILT,NO,NO
R_S_DN,100k_0805_FAIL_OFF,Resistor_SMD:R_0805_2012Metric,1=UVLO_S_PRIMARY_OK;2=PGND,CANDIDATE_NOT_BUILT,NO,NO
C_ARM,100nF_25V_DEBOUNCE_START,Capacitor_SMD:C_0603_1608Metric,1=ARM_CLOCK;2=PGND,CANDIDATE_NOT_BUILT,NO,NO
J_ESTOP_PWR,EXTERNAL_2_CONTACT_NC_ESTOP_CHANNEL_A,TerminalBlock:TerminalBlock_MaiXu_MX126-5.0-02P_1x02_P5.00mm,1=48V_FUSED;2=48V_AFTER_ESTOP,EXTERNAL_AND_UNBUILT,NO,NO
U_LATCH,TI_CD4013BE_DUAL_D_FF_ACTIVE_HIGH_ASYNC_RESET,Package_DIP:DIP-14_W7.62mm,1=LATCH_Q;10=PGND;11=PGND;12=;13=;14=VCC12;2=;3=ARM_CLOCK;4=RESET_ACTIVE;5=VCC12;6=PGND;7=PGND;8=PGND;9=PGND,CANDIDATE_NOT_BUILT,YES_PIN_OR_SYMBOL_ONLY,NO
